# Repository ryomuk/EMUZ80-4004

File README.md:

# EMUZ80-4004
4004 mezzanine board for EMUZ80

This document is written mostly in Japanese. If necessary, please use a translation service such as DeepL (I recommend this) or Google.

## 概要
電脳伝説さん(@vintagechips)のEMUZ80( https://github.com/vintagechips/emuz80 )のZ80をIntel4004に差し替えるための基板(メザニンボード)，PIC用ファームウェア，4004用のデモプログラム(電卓)です．

別レポジトリにあるIntel4004評価ボード(test4004 https://github.com/ryomuk/test4004 )の4289とROMの機能をPIC上に実装したような作りになっています．
プログラムメモリ領域のRAMは実装しておらず，データ用メモリ(4002)も2つしか搭載していないので，test4004よりも小規模なシステムですが，とりあえずデモプログラムとして電卓が動作しています．

## このレポジトリの内容
- hardware/rev0.1 : メザニンボード作成用ファイル一式(KiCad 7用)
- src/PIC/emuz80_4004.X : PIC用ファームウェア(MPLAB IDE用のプロジェクトフォルダ)
- src/demo/calc : 電卓のデモプログラム(4004アセンブラ)

## 動画
Youtubeで関連動画を公開しています．
- https://www.youtube.com/@ryomukai/videos

## ブログ
関連する情報が書いてあるかも．
- [Intel 4004 関連記事の目次@ブログの練習](https://blog.goo.ne.jp/tk-80/e/3fa1e2972737c7b7d1b83f4e7bd648a2)

## 開発環境
- [The Macroassembler AS](http://john.ccac.rwth-aachen.de:8000/as/)
- [Microchip MPLAB IDE](https://www.microchip.com/en-us/tools-resources/develop/mplab-x-ide)

## 参考にした文献，サイト等 (敬称略, 順不同)
- vintagechips, [emuz80](https://github.com/vintagechips/emuz80)
- vintagechips, [EMUZ80が完成](https://vintagechips.wordpress.com/2022/03/05/emuz80_reference/)
- satoshiokue, [EMUZ80-6502](https://github.com/satoshiokue/EMUZ80-6502)． 他，各種メザニンボード
- Gazelle, [EMUZ80用ファームウェア](https://drive.google.com/drive/folders/1NaIIpzsUY3lptekcrJjwyvWTBNHIjUf1)
- kanpapa, [emu1802](https://github.com/kanpapa/emu1802)
- yyhayami, [emuz80_yyhayami](https://github.com/yyhayami/emuz80_yyhayami)

## 更新履歴
- 2023/5/23: 初版公開

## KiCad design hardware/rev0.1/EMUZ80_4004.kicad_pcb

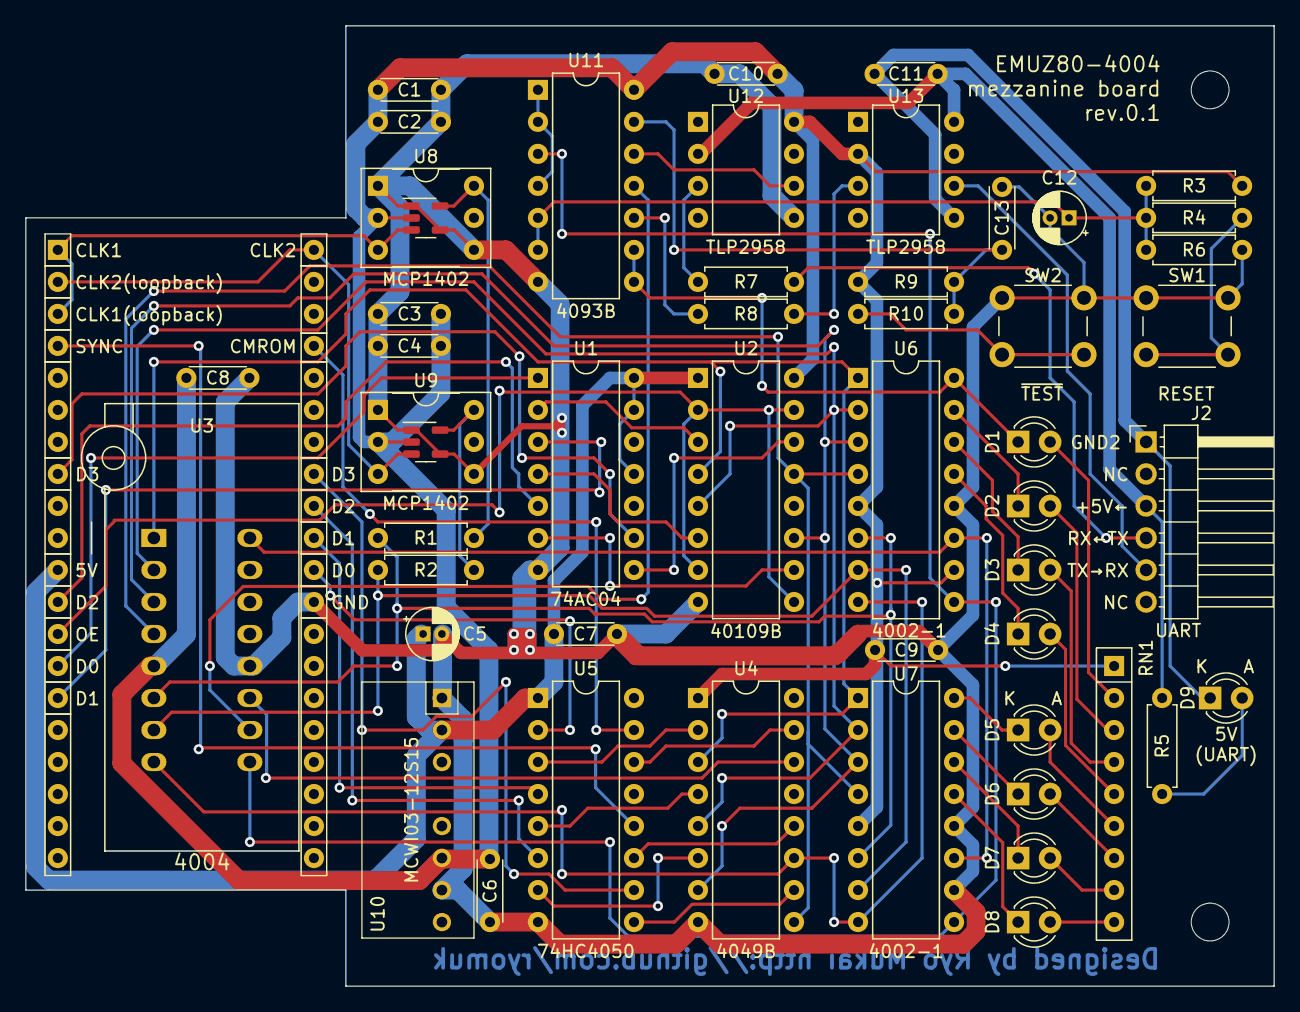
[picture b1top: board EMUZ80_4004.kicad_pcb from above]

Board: 2 copper layers, 99.1 x 76.2 mm, 50 parts (0 on the bottom side), 69 nets.

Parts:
C1, C3: 1uF; C_Disc_D4.3mm_W1.9mm_P5.00mm
C2, C4, C7, C8, C9, C10, C11: 0.1uF; C_Disc_D4.3mm_W1.9mm_P5.00mm
C5, C12: 10uF; CP_Radial_D4.0mm_P1.50mm
C6: 3.3uF; C_Disc_D4.7mm_W2.5mm_P5.00mm
C13: 1uF; C_Disc_D4.7mm_W2.5mm_P5.00mm
D1, D2, D3, D4, D5, D6, D7, D8: LED; LED_D3.0mm
D9: YELLOW; LED_D3.0mm
J1: Conn_02x20; DIP-40_W20.32mm800mil_Socket
J2: UART; PinHeader_1x06_P2.54mm_Horizontal
R1, R2: 110; R_Axial_DIN0207_L6.3mm_D2.5mm_P7.62mm_Horizontal
R3, R9: 10k; R_Axial_DIN0207_L6.3mm_D2.5mm_P7.62mm_Horizontal
R4, R7, R10: 1k; R_Axial_DIN0207_L6.3mm_D2.5mm_P7.62mm_Horizontal
R5: 47k; R_Axial_DIN0207_L6.3mm_D2.5mm_P7.62mm_Horizontal
R6: 100k; R_Axial_DIN0207_L6.3mm_D2.5mm_P7.62mm_Horizontal
R8: 4.7k; R_Axial_DIN0207_L6.3mm_D2.5mm_P7.62mm_Horizontal
RN1: 100k; R_Array_SIP9
SW1: RESET; SW_PUSH_6mm_H4.3mm
SW2: ~{TEST}; SW_PUSH_6mm_H4.3mm
U1: 74AC04; DIP-14_W7.62mm
U2: 40109B; DIP-16_W7.62mm
U3: 4004; DIP_Socket-16_W4.3_W5.08_W7.62_W10.16_W10.9_3M_216-3340-00-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
U4: 4049B; DIP-16_W7.62mm
U5: 74HC4050; DIP-16_W7.62mm
U6, U7: 4002-1; DIP-16_W7.62mm
U8, U9: MCP1402; DIP-6_W7.62mm_Socket_5pin
U10: MCWI03-12S15; SIP-8_without4pin_for_DCDC
U11: 4093B; DIP-14_W7.62mm
U12, U13: TLP2958; DIP-8_W7.62mm

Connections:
+5V: C5.1, C7.1, J1.11, U1.11, U1.13, U1.14 (VCC), U2.1 (Vcc), U5.1 (VDD), U10.2 (+VIN)
+15V: C1.2, C2.2, C3.2, C4.2, C6.1, C8.1, C9.1, C10.2, R3.1, R9.1, RN1.1 (common), U2.16 (Vdd), U3.5 (Vss), U4.1 (VCC), U6.5 (Vss), U6.10 (P0), U7.5 (Vss), U8.2 (VDD), U9.2 (VDD), U10.6 (+VOUT), U11.14 (Vdd), U12.8 (VDD), U13.2 (A)
/comport/RESET: U3.9 (RESET), U6.9 (RESET), U7.9 (RESET), U11.3
/comport/TEST: U3.10 (TEST), U11.11
/comport/TX: D1.1 (K), U6.16 (O0), U11.8, U11.9
CLKIN1: J1.1, J1.3, U8.3 (IN)
CLKIN2: J1.2, J1.40, U9.3 (IN)
CMROM: J1.37, U5.15 (O6)
DIN0: J1.30, U5.2 (O1)
DIN1: J1.31, U5.4 (O2)
DIN2: J1.32, U5.6 (O3)
DIN3: J1.33, U5.10 (O4)
DOE: J1.13, U2.2 (EN_A), U2.7 (EN_B), U2.9 (EN_C), U2.15 (EN_D)
DOUT0: J1.14, U1.1
DOUT1: J1.15, U1.3
DOUT2: J1.12, U1.5
DOUT3: J1.8, U1.9
GND: C1.1, C2.1, C3.1, C4.1, C5.2, C6.2, C7.2, C8.2, C9.2, C10.1, C12.2, C13.2, J1.29, R6.2, SW1.1, SW2.1, U1.7 (GND), U2.8 (Vss(GND)), U3.12 (Vdd), U4.8 (GND), U5.8 (VSS), U6.12 (Vdd), U7.10 (P0), U7.12 (Vdd), U8.1 (GND), U8.4 (GND), U9.1 (GND), U9.4 (GND), U10.1 (-VIN), U10.7 (-VOUT), U11.7 (Vss), U12.5 (GND)
GND2: C11.1, D9.1 (K), J2.1, U13.5 (GND)
unnamed: C12.1, R3.2, R4.2, R6.1, U11.5, U11.6
unnamed: C13.1, R9.2, R10.2, U11.13
unnamed: D1.2 (A), RN1.2 (R1)
unnamed: D2.2 (A), RN1.3 (R2)
unnamed: D2.1 (K), U6.15 (O1)
unnamed: D3.2 (A), RN1.4 (R3)
unnamed: D3.1 (K), U6.14 (O2)
unnamed: D4.2 (A), RN1.5 (R4)
unnamed: D4.1 (K), U6.13 (O3)
unnamed: D5.2 (A), RN1.6 (R5)
unnamed: D5.1 (K), U7.16 (O0)
unnamed: D6.2 (A), RN1.7 (R6)
unnamed: D6.1 (K), U7.15 (O1)
unnamed: D7.2 (A), RN1.8 (R7)
unnamed: D7.1 (K), U7.14 (O2)
unnamed: D8.2 (A), RN1.9 (R8)
unnamed: D8.1 (K), U7.13 (O3)
unnamed: D9.2 (A), R5.1
unnamed: J2.4, R7.1
unnamed: J2.5, U13.6 (Vo)
unnamed: R4.1, SW1.2
unnamed: R8.1, U11.10
unnamed: R10.1, SW2.2
unnamed: U1.2, U2.3 (A)
unnamed: U1.4, U2.6 (B)
unnamed: U1.6, U2.10 (C)
unnamed: U1.8, U2.14 (D)
unnamed: U2.4 (OUTA), U3.1 (D0), U4.3 (I1), U6.1 (D0), U7.1 (D0)
unnamed: U2.5 (OUTB), U3.2 (D1), U4.5 (I2), U6.2 (D1), U7.2 (D1)
unnamed: U2.11 (OUTC), U3.3 (D2), U4.7 (I3), U6.3 (D2), U7.3 (D2)
unnamed: U2.13 (OUTD), U3.4 (D3), U4.9 (I4), U6.4 (D3), U7.4 (D3)
unnamed: R1.2, U3.6 (CLK1), U6.6 (CLK1), U7.6 (CLK1)
unnamed: R2.2, U3.7 (CLK2), U6.7 (CLK2), U7.7 (CLK2)
unnamed: U3.16 (CMRAM0), U6.11 (CM), U7.11 (CM)
unnamed: U3.11 (CMROM), U4.14 (I6)
unnamed: U3.8 (SYNC), U4.11 (I5), U6.8 (SYNC), U7.8 (SYNC)
unnamed: U4.2 (O1), U5.3 (I1)
unnamed: U4.4 (O2), U5.5 (I2)
unnamed: U4.6 (O3), U5.7 (I3)
unnamed: U4.10 (O4), U5.9 (I4)
unnamed: U4.12 (O5), U5.11 (I5)
unnamed: U4.15 (O6), U5.14 (I6)
unnamed: R1.1, U8.5 (OUT)
unnamed: R2.1, U9.5 (OUT)
unnamed: U11.1, U11.2, U11.4
unnamed: R7.2, U12.3 (K)
unnamed: U11.12, U12.6 (Vo)
unnamed: R8.2, U13.3 (K)
SYNC: J1.4, U5.12 (O5)
VBUS: C11.2, J2.3, R5.2, U12.2 (A), U13.8 (VDD)

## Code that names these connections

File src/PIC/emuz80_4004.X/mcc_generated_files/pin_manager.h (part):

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// get/set DIN0 aliases
#define DIN0_TRIS                 TRISBbits.TRISB0
#define DIN0_LAT                  LATBbits.LATB0
#define DIN0_PORT                 PORTBbits.RB0
#define DIN0_WPU                  WPUBbits.WPUB0
#define DIN0_OD                   ODCONBbits.ODCB0
#define DIN0_ANS                  ANSELBbits.ANSELB0
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// get/set DIN1 aliases
#define DIN1_TRIS                 TRISBbits.TRISB1
#define DIN1_LAT                  LATBbits.LATB1
#define DIN1_PORT                 PORTBbits.RB1
#define DIN1_WPU                  WPUBbits.WPUB1
#define DIN1_OD                   ODCONBbits.ODCB1
#define DIN1_ANS                  ANSELBbits.ANSELB1
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// get/set DIN2 aliases
#define DIN2_TRIS                 TRISBbits.TRISB2
#define DIN2_LAT                  LATBbits.LATB2
#define DIN2_PORT                 PORTBbits.RB2
#define DIN2_WPU                  WPUBbits.WPUB2
#define DIN2_OD                   ODCONBbits.ODCB2
#define DIN2_ANS                  ANSELBbits.ANSELB2
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// get/set DIN3 aliases
#define DIN3_TRIS                 TRISBbits.TRISB3
#define DIN3_LAT                  LATBbits.LATB3
#define DIN3_PORT                 PORTBbits.RB3
#define DIN3_WPU                  WPUBbits.WPUB3
#define DIN3_OD                   ODCONBbits.ODCB3
#define DIN3_ANS                  ANSELBbits.ANSELB3
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// get/set CMROM aliases
#define CMROM_TRIS                 TRISBbits.TRISB7
#define CMROM_LAT                  LATBbits.LATB7
#define CMROM_PORT                 PORTBbits.RB7
#define CMROM_WPU                  WPUBbits.WPUB7
#define CMROM_OD                   ODCONBbits.ODCB7
#define CMROM_ANS                  ANSELBbits.ANSELB7
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// get/set DOUT0 aliases
#define DOUT0_TRIS                 TRISCbits.TRISC0
#define DOUT0_LAT                  LATCbits.LATC0
#define DOUT0_PORT                 PORTCbits.RC0
#define DOUT0_WPU                  WPUCbits.WPUC0
#define DOUT0_OD                   ODCONCbits.ODCC0
#define DOUT0_ANS                  ANSELCbits.ANSELC0
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// get/set DOUT1 aliases
#define DOUT1_TRIS                 TRISCbits.TRISC1
#define DOUT1_LAT                  LATCbits.LATC1
#define DOUT1_PORT                 PORTCbits.RC1
#define DOUT1_WPU                  WPUCbits.WPUC1
#define DOUT1_OD                   ODCONCbits.ODCC1
#define DOUT1_ANS                  ANSELCbits.ANSELC1
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// get/set DOUT2 aliases
#define DOUT2_TRIS                 TRISCbits.TRISC2
#define DOUT2_LAT                  LATCbits.LATC2
#define DOUT2_PORT                 PORTCbits.RC2
#define DOUT2_WPU                  WPUCbits.WPUC2
#define DOUT2_OD                   ODCONCbits.ODCC2
#define DOUT2_ANS                  ANSELCbits.ANSELC2
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// get/set DOUT3 aliases
#define DOUT3_TRIS                 TRISCbits.TRISC3
#define DOUT3_LAT                  LATCbits.LATC3
#define DOUT3_PORT                 PORTCbits.RC3
#define DOUT3_WPU                  WPUCbits.WPUC3
#define DOUT3_OD                   ODCONCbits.ODCC3
#define DOUT3_ANS                  ANSELCbits.ANSELC3
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// get/set DOE aliases
#define DOE_TRIS                 TRISCbits.TRISC7
#define DOE_LAT                  LATCbits.LATC7
#define DOE_PORT                 PORTCbits.RC7
#define DOE_WPU                  WPUCbits.WPUC7
#define DOE_OD                   ODCONCbits.ODCC7
#define DOE_ANS                  ANSELCbits.ANSELC7
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// get/set SYNC aliases
#define SYNC_TRIS                 TRISDbits.TRISD6
#define SYNC_LAT                  LATDbits.LATD6
#define SYNC_PORT                 PORTDbits.RD6
#define SYNC_WPU                  WPUDbits.WPUD6
#define SYNC_OD                   ODCONDbits.ODCD6
#define SYNC_ANS                  ANSELDbits.ANSELD6
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
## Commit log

2023-05-23 README updated

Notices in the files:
src/PIC/emuz80_4004.X/mcc_generated_files/pin_manager.h:
(c) 2018 Microchip Technology Inc. and its subsidiaries.
